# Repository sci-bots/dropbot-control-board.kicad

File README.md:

# DropBot v3 control board

The control board is a component of the [DropBot system][dropbot] responsible for:

* serial communication with the host computer (via USB)
* generation of the high-voltage driving signal (up to 140V @ < 10 kHz)
* impedance-measurement (for estimating drop position, velocity, etc.)
* control of other system hardware (e.g., switching boards)

For more information, please visit https://sci-bots.com

[][sci-bots]

This design is open-source hardware released under a [Creative Commons Attribution-ShareAlike licence][cc-by-sa].

[][cc-by-sa]

[dropbot]: https://github.com/sci-bots/dropbot-v3
[sci-bots]: https://sci-bots.com/
[cc-by-sa]: http://creativecommons.org/licenses/by-sa/3.0

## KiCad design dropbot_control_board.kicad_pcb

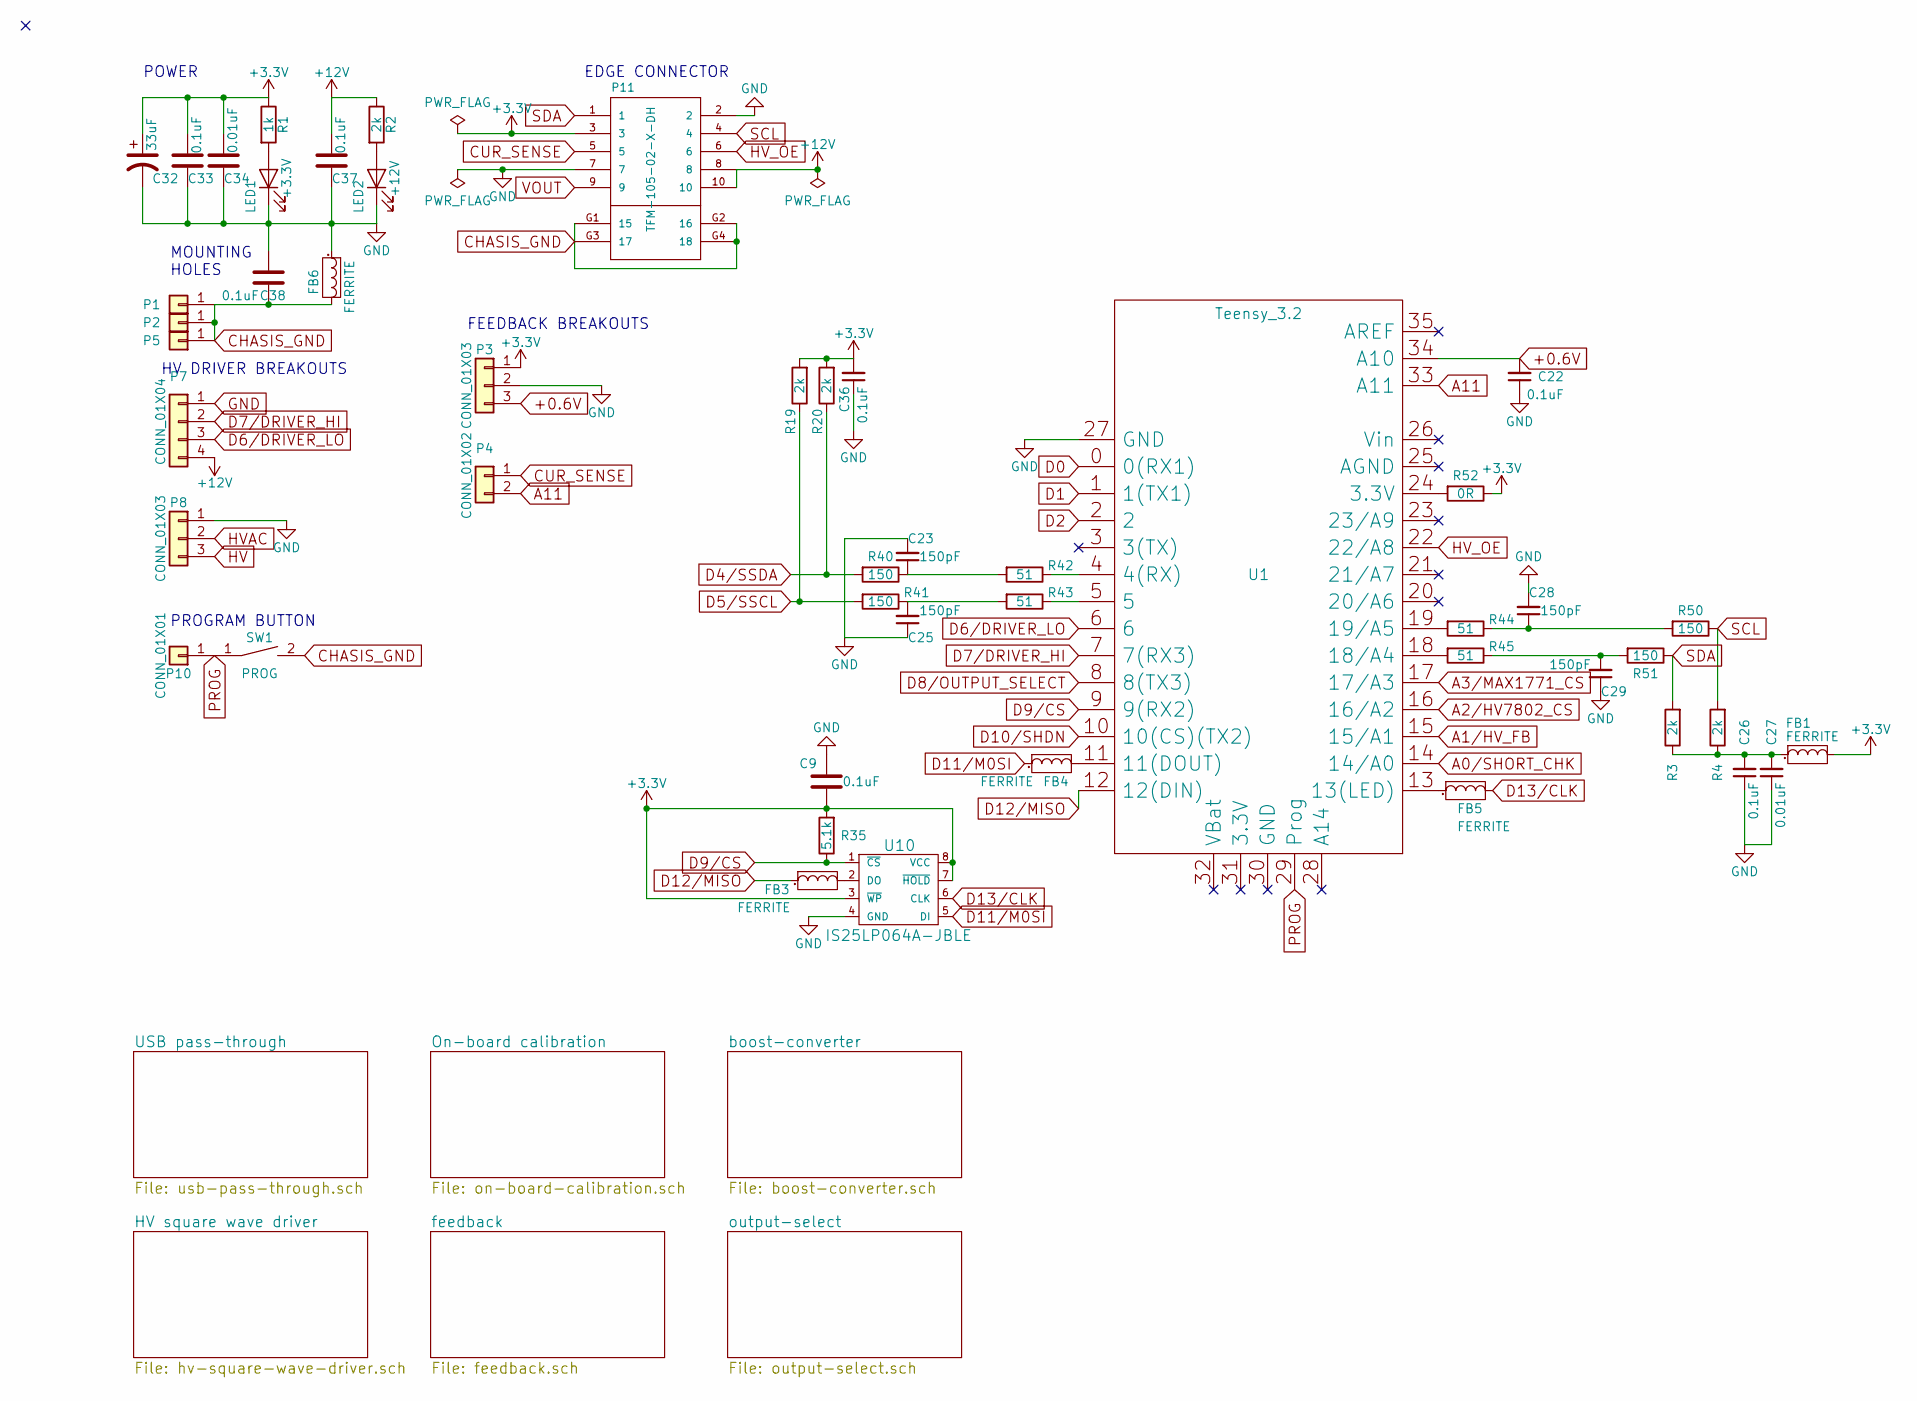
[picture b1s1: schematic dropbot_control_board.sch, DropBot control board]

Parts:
C9, C22, C26, C33, C36, C37, C38: 0.1uF; C_0805; MPN CL21B104KBCNNNC
C23, C25, C28, C29: 150pF; C_0805; MPN CL21C151JBANNNC
C27, C34: 0.01uF; C_0805; MPN CC0805KRX7R9BB103
C32: 33uF; SM2917; MPN T491D336K020AT
FB1, FB3, FB4, FB5, FB6: FERRITE; R_0805; MPN 742792040
LED1: +3.3V; LED_0805; MPN 150080BS75000
LED2: +12V; LED_0805; MPN 150080BS75000
P1, P2, P5: CONN_01X01; 1pin; MPN DNP
P3: CONN_01X03; Pin_Header_Straight_1x03_Pitch2.54mm; MPN DNP
P4: CONN_01X02; Pin_Header_Straight_1x02_Pitch2.54mm; MPN DNP
P7: CONN_01X04; Pin_Header_Straight_1x04; MPN DNP
P8: CONN_01X03; Pin_Header_Straight_1x03; MPN DNP
P10: CONN_01X01; Pin_Header_Straight_1x01_Pitch2.54mm; MPN DNP
P11: TFM-105-02-X-DH; MPN TFM-105-02-L-DH
R1: 1k; R_0805; MPN RC0805FR-071KL
R2, R3, R4, R19, R20: 2k; R_0805; MPN RC0805FR-072KL
R35: 5.1k; R_0805; MPN RC0805FR-075K1L
R40, R41, R50, R51: 150; R_0805; MPN RC0805FR-07150RL
R42, R43, R44, R45: 51; R_0805; MPN RC0805FR-0751RL
R52: 0R; R_0805; MPN RC0805JR-070RL
SW1: PROG; PTS840_GK_SMTR_LFS; MPN PTS840 GK SMTR LFS
U1: Teensy_3.2; Teensy-3.2; MPN DNP
U10: IS25LP064A-JBLE; SSO-8_5.2x5.2mm_Pitch1.27mm; MPN IS25LP064A-JBLE

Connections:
+0.6V: C22.2, P3.3, U1.34 (A10); also elsewhere on the board
+3V3: C9.1, C32.1, C33.2, C34.2, C36.2, FB1.2, P3.1, P11.3, R1.1, R19.2, R20.2, R35.2, R52.1, U10.3 (~WP), U10.7 (~HOLD), U10.8 (VCC); also elsewhere on the board
+12V: C37.2, P7.4, P11.8, P11.10, R2.1; also elsewhere on the board
A0/SHORT_CHK: U1.14 (14/A0); also elsewhere on the board
A1/HV_FB: U1.15 (15/A1); also elsewhere on the board
A2/HV7802_CS: U1.16 (16/A2); also elsewhere on the board
A3/MAX1771_CS: U1.17 (17/A3); also elsewhere on the board
A6: U1.20 (20/A6)
A7: U1.21 (21/A7)
A11: P4.2, U1.33 (A11); also elsewhere on the board
CHASIS_GND: C38.1, FB6.2, P1.1, P2.1, P5.1, P11.G1 (15), P11.G2 (16), P11.G3 (17), P11.G4 (18), SW1.2, SW1.3; also elsewhere on the board
CUR_SENSE: P4.1, P11.5; also elsewhere on the board
D0: U1.0 (0(RX1)); also elsewhere on the board
D1: U1.1 (1(TX1)); also elsewhere on the board
D2: U1.2; also elsewhere on the board
D4/SSDA: R20.1, R40.2; also elsewhere on the board
D5/SSCL: R19.1, R41.2; also elsewhere on the board
D6/DRIVER_LO: P7.3, U1.6; also elsewhere on the board
D7/DRIVER_HI: P7.2, U1.7 (7(RX3)); also elsewhere on the board
D8/OUTPUT_SELECT: U1.8 (8(TX3)); also elsewhere on the board
D9/CS: R35.1, U1.9 (9(RX2)), U10.1 (~CS)
D10/SHDN: U1.10 (10(CS)(TX2)); also elsewhere on the board
D11/M0SI: FB4.1, U10.5 (DI)
D12/MISO: FB3.1, U1.12 (12(DIN))
D13/CLK: FB5.2, U10.6 (CLK)
GND: C9.2, C22.1, C23.2, C25.1, C26.1, C27.1, C28.2, C29.1, C32.2, C33.1, C34.1, C36.1, C37.1, C38.2, FB6.1, LED1.1 (K), LED2.1 (K), P3.2, P7.1, P8.1, P11.2, P11.7, U1.27 (GND), U10.4 (GND); also elsewhere on the board
HV: P8.3; also elsewhere on the board
HVAC: P8.2; also elsewhere on the board
HV_OE: P11.6, U1.22 (22/A8); also elsewhere on the board
unnamed: C23.1, R40.1, R42.2
unnamed: C25.2, R41.1, R43.2
unnamed: C26.2, C27.2, FB1.1, R3.1, R4.1
unnamed: C28.1, R44.1, R50.2
unnamed: C29.2, R45.1, R51.2
unnamed: FB3.2, U10.2 (DO)
unnamed: FB4.2, U1.11 (11(DOUT))
unnamed: FB5.1, U1.13 (13(LED))
unnamed: LED1.2 (A), R1.2
unnamed: LED2.2 (A), R2.2
unnamed: R42.1, U1.4 (4(RX))
unnamed: R43.1, U1.5
unnamed: R44.2, U1.19 (19/A5)
unnamed: R45.2, U1.18 (18/A4)
unnamed: R52.2, U1.24 (3.3V)
PROG: P10.1, SW1.1, U1.29 (Prog)
SCL: P11.4, R4.2, R50.1
SDA: P11.1, R3.2, R51.1
VOUT: P11.9; also elsewhere on the board

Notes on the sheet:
EDGE CONNECTOR
HV DRIVER BREAKOUTS
FEEDBACK BREAKOUTS
MOUNTING HOLES
PROGRAM BUTTON
POWER

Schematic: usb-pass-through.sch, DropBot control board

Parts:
C39: 0.1uF; C_0805; MPN CL21B104KBCNNNC
D5: WE-TVS_824015; wurth-WE-TVS_SOT23-6L; MPN 824015
FB7, FB8: FERRITE; R_0805; MPN 742792040
L2: 90 Ohm@100MHz; wurth-WE-CNSW_0805; MPN 744231091
P6: USB_B; 1734346-1; MPN 1734346-1
P9: USB_A; AU-Y1006; MPN AU-Y1006

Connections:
CHASIS_GND: C39.1, D5.2 (GND), P6.4, P6.5; also elsewhere on the board
D+: L2.2, P9.3
D-: L2.3, P9.2
GND: P9.4, P9.5; also elsewhere on the board
unnamed: C39.2, FB7.2, FB8.1
unnamed: D5.1, D5.3, L2.1, P6.3
unnamed: D5.4, D5.6, L2.4, P6.2
unnamed: D5.5 (VDD), FB7.1, P6.1
unnamed: FB8.2, P9.1

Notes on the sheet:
USB PASSTHROUGH Includes ESD protection and EMI suppression (See Wurth Electronics App Note ANP002C).

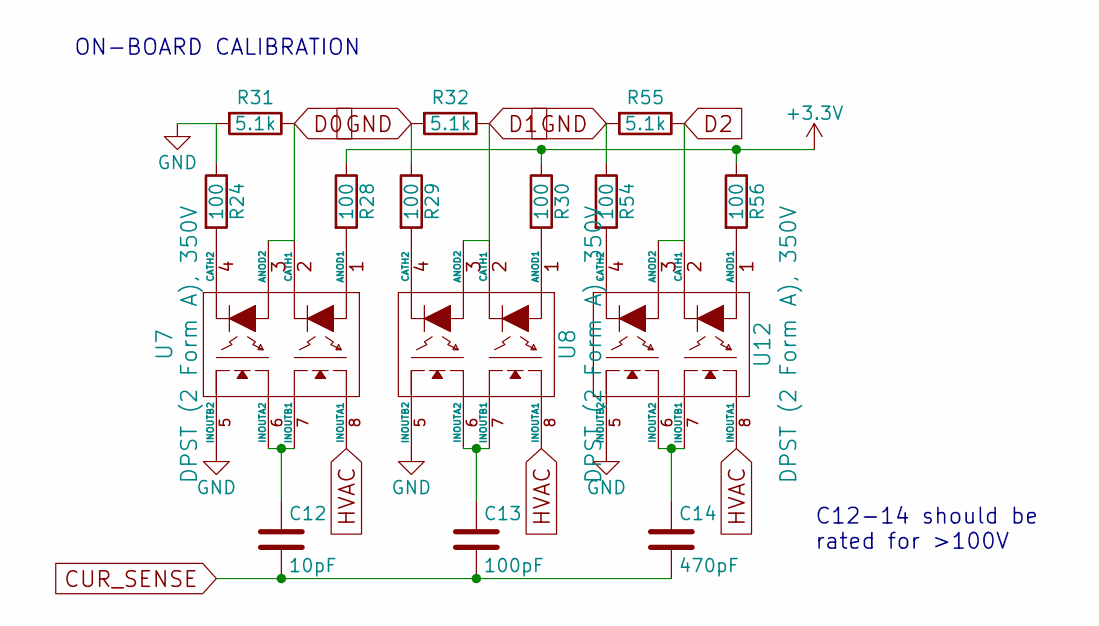
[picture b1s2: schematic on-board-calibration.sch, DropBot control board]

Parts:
C12: 10pF; C_0805; MPN CL21C100JECNNWC
C13: 100pF; C_0805; MPN CL21C101JECNNWC
C14: 470pF; C_0805; MPN CL21C471JDFNNWG
R24, R28, R29, R30, R54, R56: 100; R_0805; MPN RC0805FR-07100RL
R31, R32, R55: 5.1k; R_0805; MPN RC0805FR-075K1L
U7, U8, U12: DPST (2 Form A), 350V; DIP-8_SMD; MPN TLP227G-2(TP1,N,F)

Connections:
+3V3: R28.1, R30.1, R56.1; also elsewhere on the board
CUR_SENSE: C12.2, C13.2, C14.2; also elsewhere on the board
D0: R31.1, U7.2 (CATH1), U7.3 (ANOD2); also elsewhere on the board
D1: R32.1, U8.2 (CATH1), U8.3 (ANOD2); also elsewhere on the board
D2: R55.1, U12.2 (CATH1), U12.3 (ANOD2); also elsewhere on the board
GND: R24.1, R29.1, R31.2, R32.2, R54.1, R55.2, U7.5 (INOUTB2), U8.5 (INOUTB2), U12.5 (INOUTB2); also elsewhere on the board
HVAC: U7.8 (INOUTA1), U8.8 (INOUTA1), U12.8 (INOUTA1); also elsewhere on the board
unnamed: C12.1, U7.6 (INOUTA2), U7.7 (INOUTB1)
unnamed: C13.1, U8.6 (INOUTA2), U8.7 (INOUTB1)
unnamed: C14.1, U12.6 (INOUTA2), U12.7 (INOUTB1)
unnamed: R24.2, U7.4 (CATH2)
unnamed: R28.2, U7.1 (ANOD1)
unnamed: R29.2, U8.4 (CATH2)
unnamed: R30.2, U8.1 (ANOD1)
unnamed: R54.2, U12.4 (CATH2)
unnamed: R56.2, U12.1 (ANOD1)

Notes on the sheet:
ON-BOARD CALIBRATION
C12-14 should be rated for >100V

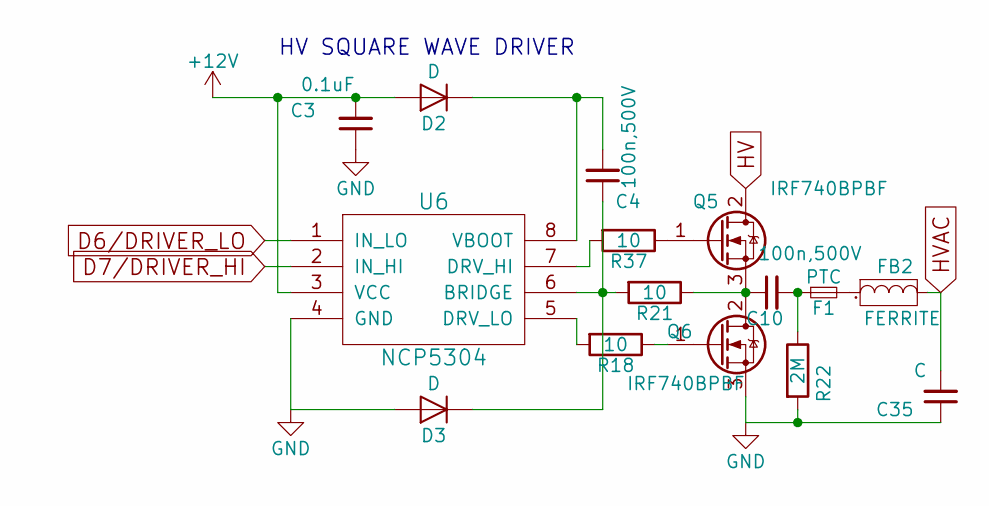
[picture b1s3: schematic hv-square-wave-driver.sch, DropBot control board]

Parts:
C3: 0.1uF; C_0805; MPN CL21B104KBCNNNC
C4, C10: 100n,500V; C_1210; MPN C1210C104KCRACTU
C35: C; C_1206; MPN DNP
D2, D3: D; SMA_Standard; MPN US1J-13-F
F1: PTC; Resistor_Vertical_RM5mm; MPN B59773B0120A070
FB2: FERRITE; R_0805; MPN 742792040
Q5, Q6: IRF740BPBF; TO-220_Neutral123_Horizontal_LargePads; MPN IRF740BPBF
R18, R21, R37: 10; R_0805; MPN RC0805FR-0710RL
R22: 2M; R_1206; MPN HVCB1206KDL2M00
U6: NCP5304; SOIC-8-N; MPN NCP5304DR2G

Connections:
+12V: C3.2, D2.2 (A), U6.3 (VCC); also elsewhere on the board
D6/DRIVER_LO: U6.1 (IN_LO); also elsewhere on the board
D7/DRIVER_HI: U6.2 (IN_HI); also elsewhere on the board
GND: C3.1, C35.1, D3.2 (A), Q6.3 (S), R22.2, U6.4 (GND); also elsewhere on the board
HV: Q5.2 (D); also elsewhere on the board
HVAC: C35.2, FB2.2; also elsewhere on the board
unnamed: C4.1, D3.1 (K), R21.2, U6.6 (BRIDGE)
unnamed: C4.2, D2.1 (K), U6.8 (VBOOT)
unnamed: C10.1, Q5.3 (S), Q6.2 (D), R21.1
unnamed: C10.2, F1.1, R22.1
unnamed: F1.2, FB2.1
unnamed: Q5.1 (G), R37.1
unnamed: Q6.1 (G), R18.1
unnamed: R18.2, U6.5 (DRV_LO)
unnamed: R37.2, U6.7 (DRV_HI)

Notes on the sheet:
HV SQUARE WAVE DRIVER

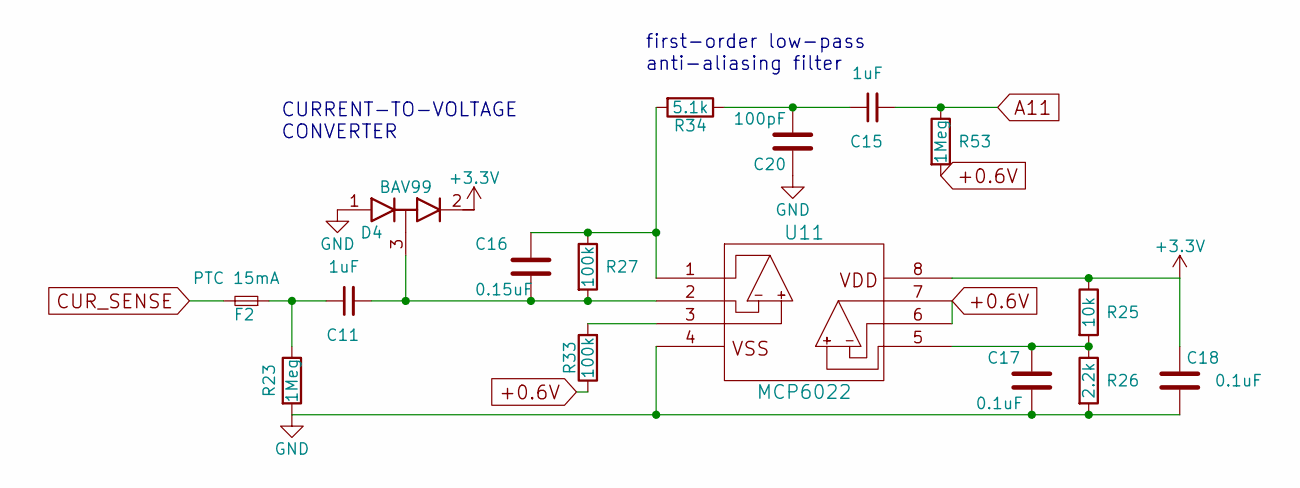
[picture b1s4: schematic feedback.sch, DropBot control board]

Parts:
C11, C15: 1uF; C_0805; MPN CC0805KKX7R9BB105
C16: 0.15uF; C_0805; MPN 08053C154JAT2A
C17, C18: 0.1uF; C_0805; MPN CL21B104KBCNNNC
C20: 100pF; C_0805; MPN CL21C101JECNNWC
D4: BAV99; SOT-23; MPN TBAV99,LM
F2: PTC 15mA; R_1210; MPN B59807A0090A062
R23, R53: 1Meg; R_0805; MPN RC0805FR-071ML
R25: 10k; R_0805; MPN RC0805FR-0710KL
R26: 2.2k; R_0805; MPN RC0805FR-072K2L
R27, R33: 100k; R_0805; MPN RC0805FR-07100KL
R34: 5.1k; R_0805; MPN RC0805FR-075K1L
U11: MCP6022; DIP-8_W7.62mm; MPN ED08DT

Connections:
+0.6V: R33.1, R53.2, U11.6 (VINB-), U11.7 (VOUTB); also elsewhere on the board
+3V3: C18.1, D4.2 (K), R25.1, U11.8 (VDD); also elsewhere on the board
A11: C15.2, R53.1; also elsewhere on the board
CUR_SENSE: F2.2; also elsewhere on the board
GND: C17.2, C18.2, C20.1, D4.1 (A), R23.2, R26.2, U11.4 (VSS); also elsewhere on the board
unnamed: C11.1, F2.1, R23.1
unnamed: C11.2, C16.2, D4.3 (common), R27.2, U11.2 (VINA-)
unnamed: C15.1, C20.2, R34.1
unnamed: C16.1, R27.1, R34.2, U11.1 (VOUTA)
unnamed: C17.1, R25.2, R26.1, U11.5 (VINB+)
unnamed: R33.2, U11.3 (VINA+)

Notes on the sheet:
first-order low-pass anti-aliasing filter
CURRENT-TO-VOLTAGE CONVERTER

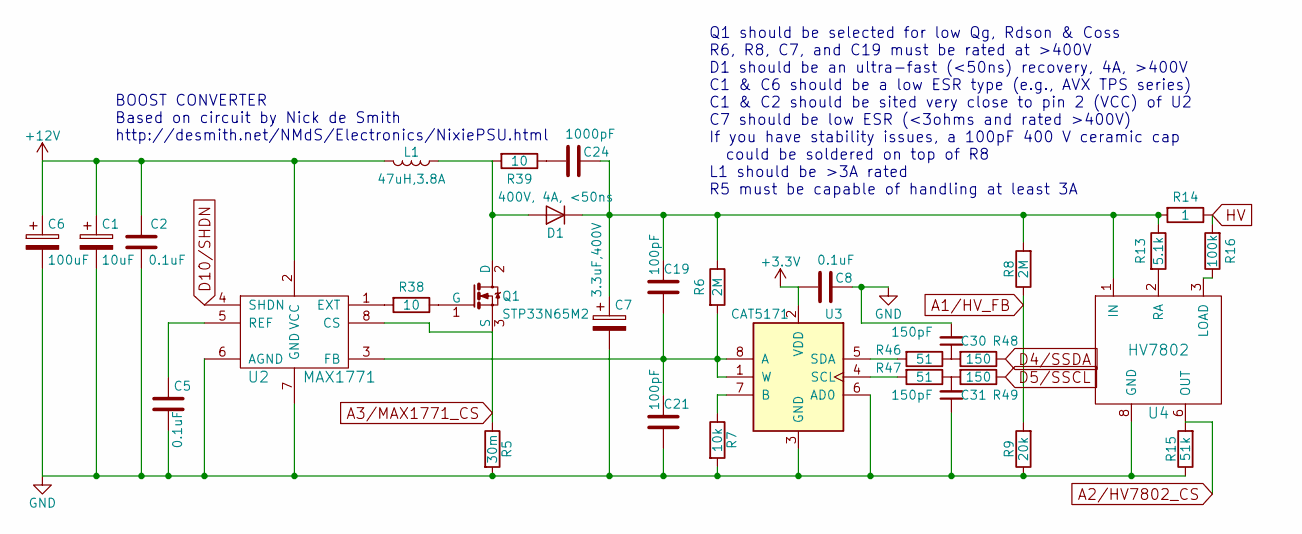
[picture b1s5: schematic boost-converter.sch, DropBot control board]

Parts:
C1: 10uF; TantalC_SizeD_EIA-7343_Reflow; MPN T494D106M025AT
C2, C5, C8: 0.1uF; C_0805; MPN CL21B104KBCNNNC
C6: 100uF; TantalC_SizeE_EIA-7360_Reflow; MPN T491X107K025AT
C7: 3.3uF,400V; c_elec_10x10; MPN EEV-EB2G3R3Q
C19, C21: 100pF; C_0805; MPN CL21C101JECNNWC
C24: 1000pF; C_0805; MPN 501R15W102KV4E
C30, C31: 150pF; C_0805; MPN CL21C151JBANNNC
D1: 400V, 4A, <50ns; SMC_Standard; MPN VS-4EGU06-M3/5BT
L1: 47uH,3.8A; SRR1210; MPN SRR1210-470M
Q1: STP33N65M2; TO-220_Neutral123_Horizontal_LargePads; MPN STP33N65M2
R5: 30m; R_2512; MPN CSR2512C0R03F
R6, R8: 2M; R_1206; MPN HVCB1206KDL2M00
R7: 10k; R_0805; MPN RC0805FR-0710KL
R9: 20k; R_0805; MPN RC0805FR-0720KL
R13: 5.1k; R_0805; MPN RC0805FR-075K1L
R14: 1; R_0805; MPN ERJ-6DQJ1R0V
R15: 51k; R_0805; MPN RC0805FR-0751KL
R16: 100k; R_0805; MPN RC0805FR-07100KL
R38, R39: 10; R_0805; MPN RC0805FR-0710RL
R46, R47: 51; R_0805; MPN RC0805FR-0751RL
R48, R49: 150; R_0805; MPN RC0805FR-07150RL
U2: MAX1771; SOIC-8_3.9x4.9mm_Pitch1.27mm; MPN MAX1771ESA+
U3: CAT5171; SOT-23-8; MPN CAT5171TBI-50GT3
U4: HV7802; MSOP-8; MPN HV7802MG-G

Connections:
+3V3: C8.2, U3.2 (VDD); also elsewhere on the board
+12V: C1.1, C2.2, C6.1, L1.2, U2.2 (VCC); also elsewhere on the board
A1/HV_FB: R8.1, R9.2; also elsewhere on the board
A2/HV7802_CS: R15.2, U4.6 (OUT); also elsewhere on the board
A3/MAX1771_CS: Q1.3 (S), R5.1, U2.8 (CS); also elsewhere on the board
D4/SSDA: R48.1; also elsewhere on the board
D5/SSCL: R49.1; also elsewhere on the board
D10/SHDN: U2.4 (SHDN); also elsewhere on the board
GND: C1.2, C2.1, C5.2, C6.2, C7.2, C8.1, C21.1, C30.2, C31.1, R5.2, R7.2, R9.1, R15.1, U2.6 (AGND), U2.7 (GND), U3.3 (GND), U3.6 (AD0), U4.8 (GND); also elsewhere on the board
HV: R14.1, R16.2; also elsewhere on the board
unnamed: C5.1, U2.5 (REF)
unnamed: C19.1, C21.2, R6.2, U2.3 (FB), U3.1 (W), U3.8 (A)
unnamed: C7.1, C19.2, C24.1, D1.1 (K), R6.1, R8.2, R13.1, R14.2, U4.1 (IN)
unnamed: C24.2, R39.1
unnamed: C30.1, R46.1, R48.2
unnamed: C31.2, R47.1, R49.2
unnamed: D1.2 (A), L1.1, Q1.2 (D), R39.2
unnamed: Q1.1 (G), R38.1
unnamed: R7.1, U3.7 (B)
unnamed: R13.2, U4.2 (RA)
unnamed: R16.1, U4.3 (LOAD)
unnamed: R38.2, U2.1 (EXT)
unnamed: R46.2, U3.5 (SDA)
unnamed: R47.2, U3.4 (SCL)

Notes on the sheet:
BOOST CONVERTER Based on circuit by Nick de Smith http://desmith.net/NMdS/Electronics/NixiePSU.html
Q1 should be selected for low Qg, Rdson & Coss R6, R8, C7, and C19 must be rated at >400V D1 should be an ultra-fast (<50ns) recovery, 4A, >400V C1 & C6 should be a low ESR type (e.g., AVX TPS series) C1 & C2 should be sited very close to pin 2 (VCC) of U2 C7 should be low ESR (<3ohms and rated >40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

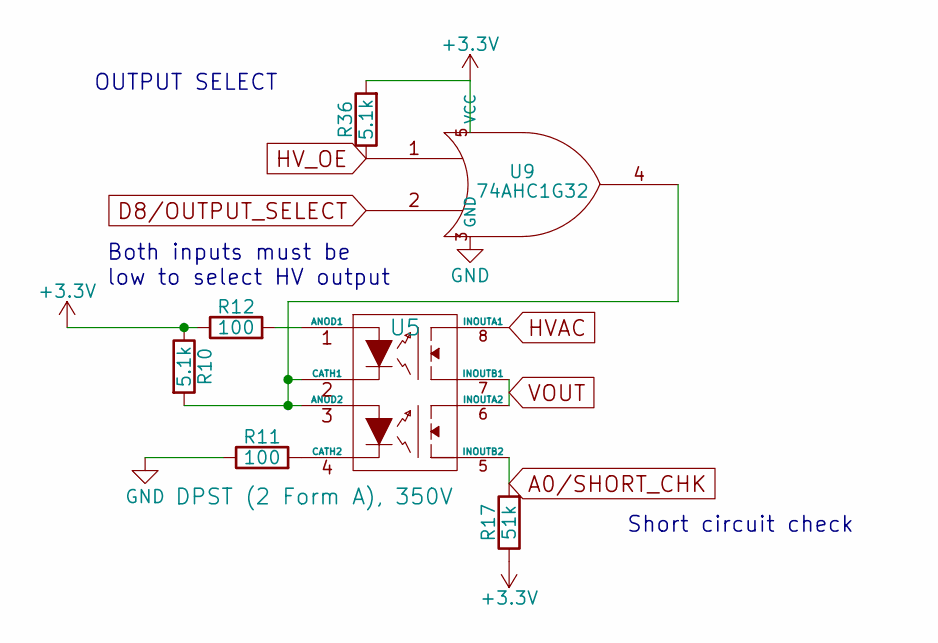
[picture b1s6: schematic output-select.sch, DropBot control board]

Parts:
R10, R36: 5.1k; R_0805; MPN RC0805FR-075K1L
R11, R12: 100; R_0805; MPN RC0805FR-07100RL
R17: 51k; R_0805; MPN RC0805FR-0751KL
U5: DPST (2 Form A), 350V; DIP-8_SMD; MPN TLP227G-2(TP1,N,F)
U9: 74AHC1G32; SOT-353; MPN 74AHC1G32GW,125

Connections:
+3V3: R10.1, R12.1, R17.1, R36.2, U9.5 (VCC); also elsewhere on the board
A0/SHORT_CHK: R17.2, U5.5 (INOUTB2); also elsewhere on the board
D8/OUTPUT_SELECT: U9.2; also elsewhere on the board
GND: R11.1, U9.3 (GND); also elsewhere on the board
HVAC: U5.8 (INOUTA1); also elsewhere on the board
HV_OE: R36.1, U9.1; also elsewhere on the board
unnamed: R10.2, U5.2 (CATH1), U5.3 (ANOD2), U9.4
unnamed: R11.2, U5.4 (CATH2)
unnamed: R12.2, U5.1 (ANOD1)
VOUT: U5.6 (INOUTA2), U5.7 (INOUTB1); also elsewhere on the board

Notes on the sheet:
OUTPUT SELECT
Both inputs must be low to select HV output
Short circuit check

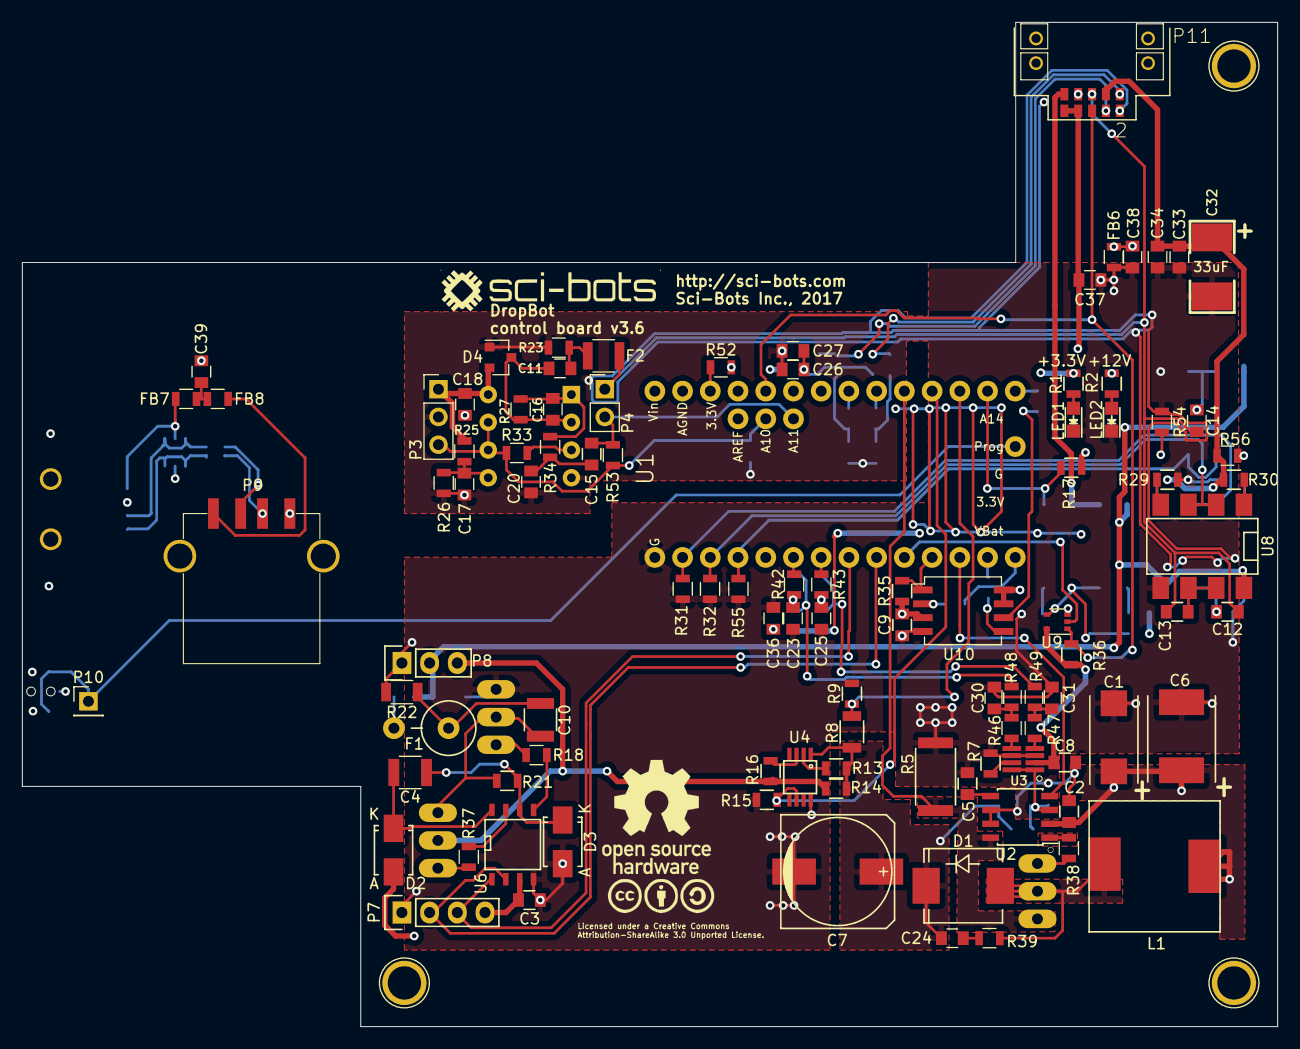
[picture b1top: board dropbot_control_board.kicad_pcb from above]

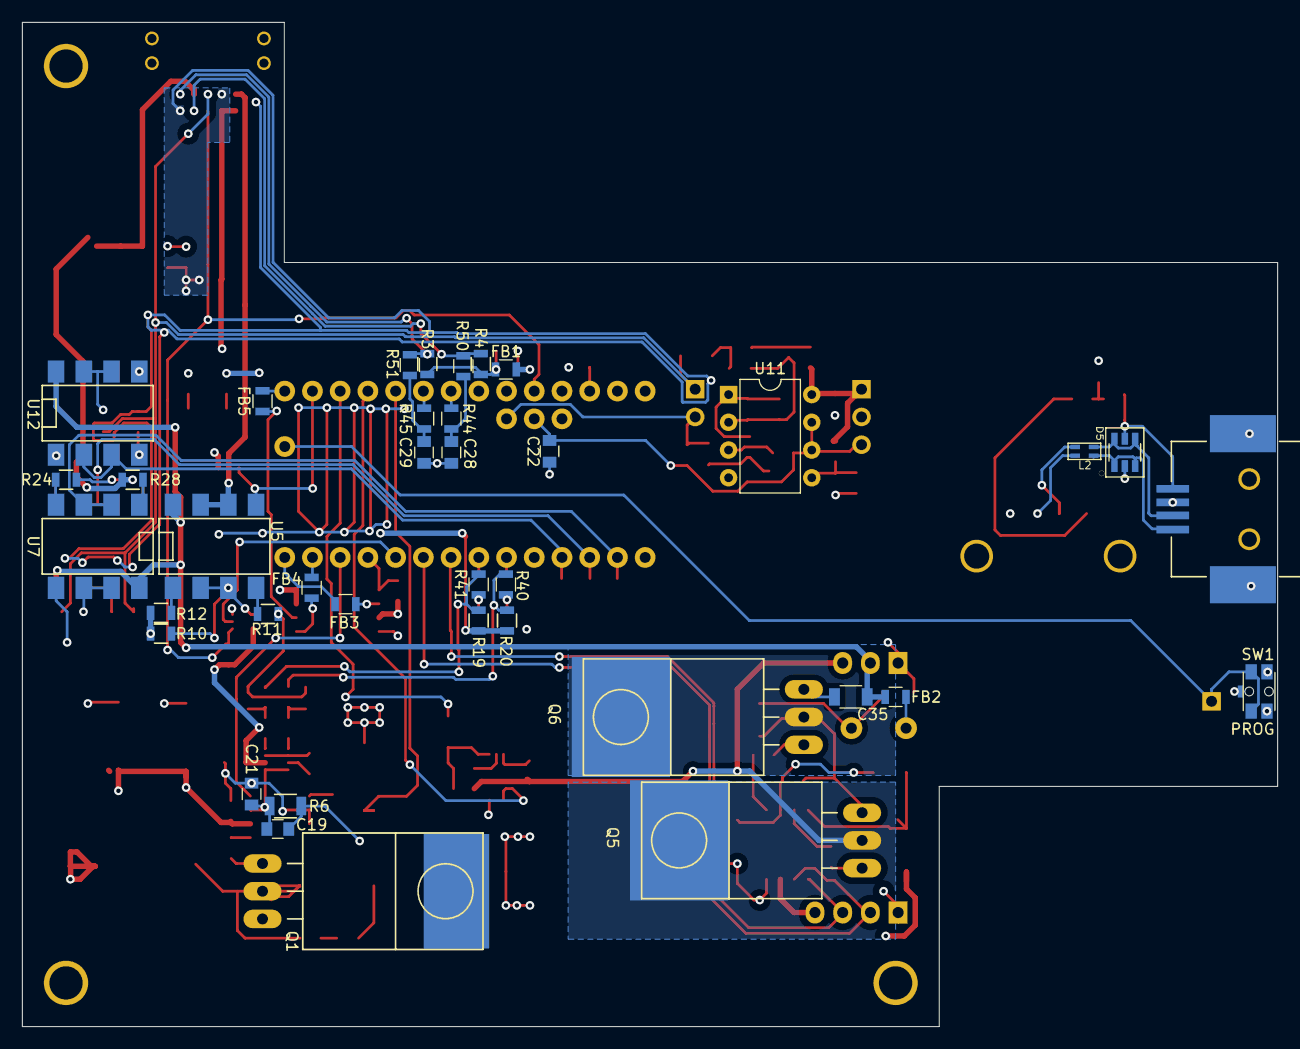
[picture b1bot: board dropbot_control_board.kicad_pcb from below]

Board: 4 copper layers, 115.0 x 92.0 mm, 141 parts (38 on the bottom side), 94 nets.

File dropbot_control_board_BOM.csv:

Reference,Value,Footprint,Count,Datasheet,Mfg_Part_No
"LED2, LED1","+12V, +3.3V",LEDs:LED_0805,2,,150080BS75000
"R2, R3, R4, R19, R20",2k,Resistors_SMD:R_0805,5,,RC0805FR-072KL
R1,1k,Resistors_SMD:R_0805,1,,RC0805FR-071KL
P8,CONN_01X03,Pin_Headers:Pin_Header_Straight_1x03,1,,
P7,CONN_01X04,Pin_Headers:Pin_Header_Straight_1x04,1,,
"R35, R31, R32, R55, R34, R13, R10, R36",5.1k,Resistors_SMD:R_0805,8,,RC0805FR-075K1L
U10,IS25LP064A-JBLE,Sci-Bots:SSO-8_5.2x5.2mm_Pitch1.27mm,1,https://www.winbond.com/resource-files/w25q64fv%20revq%20061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,IS25LP064A-JBLE
"C9, C26, C33, C36, C37, C38, C22, C39, C3, C17, C18, C5, C8, C2",0.1uF,Capacitors_SMD:C_0805,14,,CL21B104KBCNNNC
P11,TFM-105-02-X-DH,Sci-Bots:TFM-105-02-X-DH,1,,TFM-105-02-L-DH
"R45, R44, R43, R42, R46, R47",51,Resistors_SMD:R_0805,6,,RC0805FR-0751RL
"C28, C29, C25, C23, C30, C31",150pF,Capacitors_SMD:C_0805,6,,CL21C151JBANNNC
"R51, R50, R41, R40, R48, R49",150,Resistors_SMD:R_0805,6,,RC0805FR-07150RL
"FB1, FB4, FB3, FB5, FB6, FB7, FB8, FB2","FERRITE, 600 Ohm@100MHz, 600 Ohm@100MHz, FERRITE",Resistors_SMD:R_0805,8,,742792040
"C27, C34",0.01uF,Capacitors_SMD:C_0805,2,,CC0805KRX7R9BB103
C32,33uF,Sci-Bots:SM2917,1,,T491D336K020AT
"P1, P2, P5",CONN_01X01,Connect:1pin,3,,
U1,Teensy_3.2,Sci-Bots:Teensy-3.2,1,,
R52,0R,Resistors_SMD:R_0805,1,,RC0805JR-070RL
SW1,PROG,Sci-Bots:PTS840_GK_SMTR_LFS,1,,PTS840 GK SMTR LFS
P10,CONN_01X01,Pin_Headers:Pin_Header_Straight_1x01_Pitch2.54mm,1,,
P3,CONN_01X03,Pin_Headers:Pin_Header_Straight_1x03_Pitch2.54mm,1,,
P4,CONN_01X02,Pin_Headers:Pin_Header_Straight_1x02_Pitch2.54mm,1,,
D5,WE-TVS_824015,Sci-Bots:wurth-WE-TVS_SOT23-6L,1,,824015
L2,90 Ohm@100MHz,Sci-Bots:wurth-WE-CNSW_0805,1,,744231091
P6,USB_B,Sci-Bots:1734346-1,1,,1734346-1
P9,USB_A,Sci-Bots:AU-Y1006,1,,AU-Y1006
"U7, U8, U12, U5","DPST (2 Form A), 350V",SMD_Packages:DIP-8_SMD,4,,"TLP227G-2(TP1,N,F)"
C12,10pF,Capacitors_SMD:C_0805,1,,CL21C100JECNNWC
"R24, R28, R29, R30, R54, R56, R12, R11",100,Resistors_SMD:R_0805,8,,RC0805FR-07100RL
"C13, C20, C19, C21",100pF,Capacitors_SMD:C_0805,4,,CL21C101JECNNWC
C14,470pF,Capacitors_SMD:C_0805,1,,CL21C471JDFNNWG
U6,NCP5304,SMD_Packages:SOIC-8-N,1,,NCP5304DR2G
"D2, D3",D,Diodes_SMD:SMA_Standard,2,,US1J-13-F
"R21, R37, R18, R38, R39",10,Resistors_SMD:R_0805,5,,RC0805FR-0710RL
"R22, R6, R8",2M,Resistors_SMD:R_1206,3,,HVCB1206KDL2M00
"Q5, Q6",IRF740BPBF,TO_SOT_Packages_THT:TO-220_Neutral123_Horizontal_LargePads,2,,IRF740BPBF
"C4, C10","100n,500V",Capacitors_SMD:C_1210,2,,C1210C104KCRACTU
C35,C,Capacitors_SMD:C_1206,1,,
F1,PTC,Resistors_ThroughHole:Resistor_Vertical_RM5mm,1,,B59773B0120A070
"R25, R7",10k,Resistors_SMD:R_0805,2,,RC0805FR-0710KL
R26,2.2k,Resistors_SMD:R_0805,1,,RC0805FR-072K2L
"R27, R33, R16",100k,Resistors_SMD:R_0805,3,,RC0805FR-07100KL
C16,0.15uF,Capacitors_SMD:C_0805,1,,08053C154JAT2A
"R23, R53",1Meg,Resistors_SMD:R_0805,2,,RC0805FR-071ML
F2,PTC 15mA,Resistors_SMD:R_1210,1,,B59807A0090A062
D4,BAV99,TO_SOT_Packages_SMD:SOT-23,1,,"TBAV99,LM"
"C11, C15",1uF,Capacitors_SMD:C_0805,2,,CC0805KKX7R9BB105
U11,MCP6022,Housings_DIP:DIP-8_W7.62mm,1,,ED08DT
C6,100uF,Capacitors_Tantalum_SMD:TantalC_SizeE_EIA-7360_Reflow,1,,T491X107K025AT
L1,"47uH,3.8A",footprints:SRR1210,1,,SRR1210-470M
D1,"400V, 4A, <50ns",Diodes_SMD:SMC_Standard,1,,VS-4EGU06-M3/5BT
C7,"3.3uF,400V",Capacitors_SMD:c_elec_10x10,1,,EEV-EB2G3R3Q
U2,MAX1771,Housings_SOIC:SOIC-8_3.9x4.9mm_Pitch1.27mm,1,,MAX1771ESA+ 
Q1,STP33N65M2,TO_SOT_Packages_THT:TO-220_Neutral123_Horizontal_LargePads,1,,STP33N65M2
R5,30m,Resistors_SMD:R_2512,1,,CSR2512C0R03F
R9,20k,Resistors_SMD:R_0805,1,,RC0805FR-0720KL
U4,HV7802,footprints:MSOP-8,1,,HV7802MG-G
R14,1,Resistors_SMD:R_0805,1,,ERJ-6DQJ1R0V
"R15, R17",51k,Resistors_SMD:R_0805,2,,RC0805FR-0751KL
C1,10uF,Capacitors_Tantalum_SMD:TantalC_SizeD_EIA-7343_Reflow,1,,T494D106M025AT
U3,CAT5171,Sci-Bots:SOT-23-8,1,http://www.onsemi.com/pub_link/Collateral/CAT5171-D.PDF,CAT5171TBI-50GT3
C24,1000pF,Capacitors_SMD:C_0805,1,,501R15W102KV4E
U9,74AHC1G32,TO_SOT_Packages_SMD:SOT-353,1,http://www.nxp.com/documents/data_sheet/74AHC_AHCT1G32.pdf,"74AHC1G32GW,125"

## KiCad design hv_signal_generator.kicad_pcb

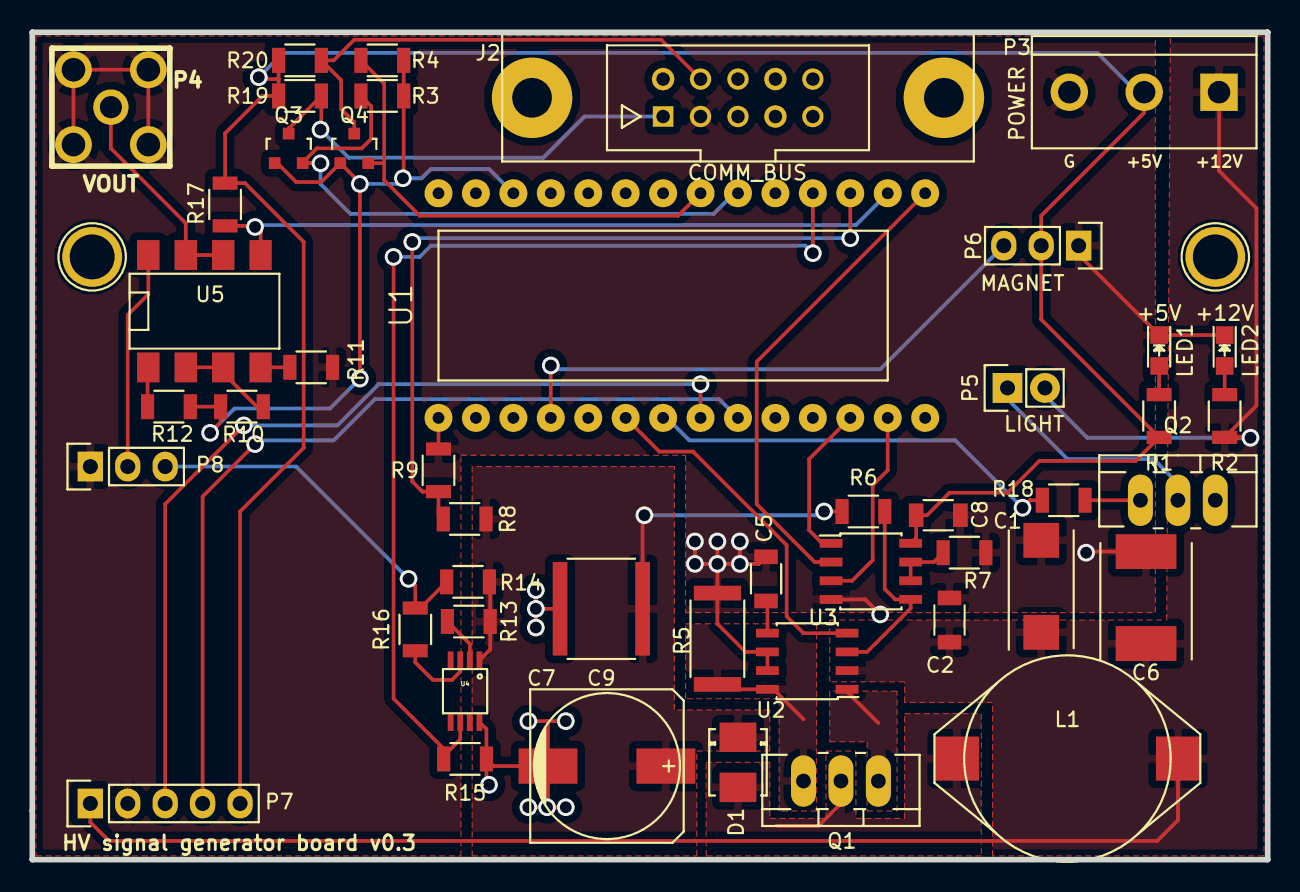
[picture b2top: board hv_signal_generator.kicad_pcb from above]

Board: 2 copper layers, 83.8 x 56.1 mm, 47 parts (0 on the bottom side), 38 nets.

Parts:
C1: 10uF; TantalC_SizeD_EIA-7343_Reflow
C2, C5, C8: 0.1uF; C_1206
C6: 100uF,35V; TantalC_SizeE_EIA-7360_Reflow
C7: 3.3uF,400V; c_elec_10x10
C9: 100nF,400V; C_2225
D1: ES2F; DO-214BA
J2: COMM_BUS; he10-10d
L1: 100uH; DU1971
LED1: +5V; LED_0805
LED2: +12V; LED_0805
P3: POWER; bornier3
P4: VOUT; JACK_SMA
P5: LIGHT; Pin_Header_Straight_1x02
P6: MAGNET; Pin_Header_Straight_1x03
P7: CONN_01X05; Pin_Header_Straight_1x05
P8: CONN_01X03; Pin_Header_Straight_1x03
Q1: IRF644PBF; TO-220_Neutral123_Vertical_LargePads
Q2: TIP120; TO-220_Neutral123_Vertical_LargePads
Q3, Q4: 2N7002; SOT-23
R1, R18: 1k; R_1206
R2: 2k; R_1206
R3, R4, R13, R19, R20: 5.1k; R_1206
R5: 50m; R_2512
R6, R8: 1M; R_1206
R7: 4k; R_1206
R9: 20k; R_1206
R10: 4.75k; R_1206
R11, R12: 200; R_1206
R14: 5.1; R_1206
R15, R17: 51k; R_1206
R16: 100k; R_1206
U1: Teensy_3.1; Teensy-3.1
U2: MAX1771; SOIC-8_3.9x4.9mm_Pitch1.27mm
U3: MCP41050; SOIC-8_3.9x4.9mm_Pitch1.27mm
U4: HV7802; MSOP-8
U5: AQW216; DIP-8_SMD

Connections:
+3.3V: Q3.1, Q4.1, R3.1, R4.1, R10.1, R12.2, U1.24
+5V: C8.2, P3.2, P6.2, P7.5, R1.1, R17.1, R19.1, R20.1, U3.8
+12V: C1.1, C2.1, C6.1, L1.2, P3.1, P5.2, P7.1, R2.1, U2.2
A0/SHORT_CHK: R17.2, U1.14, U5.5
A1/HV_FB: R8.1, R9.2, U1.15
A2/CURRENT_SENSE: R15.2, U1.16, U4.6
A3/OUTPUT_SELECT: R10.2, U5.2, U5.3
D2/SERVO: P6.3, U1.2
D4/SHDN: U1.4, U2.4
D5/LED: R18.2, U1.5
D6/DRIVER_HI: P7.3, U1.6
D7/DRIVER_LO: P7.4, U1.7
D10/MCP41050_CS: U1.10, U3.1
D11/MOSI: U1.11, U3.3
D13/SCK: U1.13, U3.2
GND: C1.2, C2.2, C5.2, C6.2, C7.2, C8.1, C9.2, J2.3, LED1.1, LED2.1, P3.3, P4.2, P6.1, P7.2, P8.1, Q2.3, R5.2, R7.2, R9.1, R11.1, R15.1, U1.27, U2.6, U2.7, U3.4, U4.8
HV: P8.3, R14.1, R16.2
unnamed: C5.1, U2.5
unnamed: C7.1, C9.1, D1.1, R6.1, R8.2, R13.1, R14.2, U4.1
unnamed: D1.2, L1.1, Q1.2
unnamed: LED1.2, R1.2
unnamed: LED2.2, R2.2
unnamed: P4.1, U5.6, U5.7
unnamed: P5.1, Q2.2
unnamed: Q1.1, U2.1
unnamed: Q1.3, R5.1, U2.8
unnamed: Q2.1, R18.1
unnamed: R6.2, U2.3, U3.5
unnamed: R7.1, U3.6, U3.7
unnamed: R11.2, U5.4
unnamed: R12.1, U5.1
unnamed: R13.2, U4.2
unnamed: R16.1, U4.3
SCL_3.3V: Q4.2, R4.2, U1.19
SCL_5V: J2.4, Q4.3, R20.2
SDA_3.3V: Q3.2, R3.2, U1.18
SDA_5V: J2.1, Q3.3, R19.2
VOUT: P8.2, U5.8

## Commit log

2016-02-17 Complete layout
2016-02-17 Move C1 and C2 closer to MAX1771 chip and ...
    Add layout notes
2016-02-17 Add clearance between VOUT pin and screw
2016-02-18 Add part numbers to schematic`
2016-04-13 [WIP] Remove HV513, fix orientation of FTDI header
    * fix footprint of L1
2016-04-15 [WIP] Add hv signal generator breakout headers
2016-04-15 Swap parts to support up to 400V and use BJT for LED
2016-04-16 Swap ATMEGA328 for Teensy
2016-04-16 Suppress leading zeros in drill file
2016-04-25 Replace footprint for transistors with SOT-23
2016-09-20 Rename dropbot-control-board
2016-09-21 Fix routing of D3/OUTPUT_SELECT and add MAX1771...
    Fix routing of D3/OUTPUT_SELECT and add MAX1771 current sensing.
2016-09-21 Connect 5V pin on COMM_BUS
2016-09-21 [WIP] Integrate HV square-wave driver (not routed)
2016-09-21 [WIP] Add feedback circuit and on-board calibration
2016-09-22 Re-do layout
2016-09-25 Bump library version
2016-11-23 Minor fixes
    * fix inductor footprint
    * footprints for various HV resistors
    * labels for some resistors/caps
    * remove shorted +12V trace
2016-12-19 Use edge connectors and ...
    * Add SPI flash memory
    * Add HV output enable
    * Make feedback circuit breakout and use DIP op-amp
    * Pass Teensy's USB signals through edge connector
2016-12-19 Update pdfs
2016-12-19 Remove rescue library
2017-01-05 Update BOM
2017-01-05 Fix BOM
2017-01-05 Fix op-amp package in BOM
2017-03-07 EMC related improvements
    * convert to 4-layer board
    * add jumper to connect 3.3V of Teensy
    * put filters on i2c
    * add guard traces around i2c and current-sense lines
    * add ferrites to SPI lines
    * add snubber on SPMS diode
2017-03-16 Lower the resistance of i2c pullups (4.75k --> 2k)
2017-03-21 Add usb passthrough, reset button, ...
    * add usb passthrough
    * add reset button
    * fix bad trace on U5
    * fix part number for C7 (3.3uF instead of 10uF)
2017-04-04 Swap F2 for higher voltage rating, monitor HV_OE
    * swap F2 for 1210 footprint: B59807A90A62 (higher voltage rating)
    * monitor HV_OE with A8
2017-04-05 Change part numbers for i2c filters
2017-04-18 Update BOM with alternate parts for C6 and D4
    These parts were out of stock at Digi-key as of 2017-04-18.
2017-04-20 Update current limit on F2
2017-04-21 Change component for D1
2017-04-25 [WIP] Fix USB-B footprint (P6)
    Fixes #3
2017-04-25 [WIP] Fixes #1: C18 is disconnected
2017-04-25 [WIP] Fixes #2: Change prefixes for J1 and IC1
2017-04-25 [WIP] Silkscreen fixes (Fixes #4)
2017-04-25 Move USB-B and program switch up 1mm
2017-05-17 Fix feedback and on-board calibration and move USB
2017-06-02 Add missing schematic diagrams and change some part numbers
2017-06-05 Change part number for ferrites, add *.pos files
2017-06-19 Improve layout/stability of boost converter, etc.
    * improve layout/stability of boost converter
    * enable on board calibration without HVOE
    * add decoupling cap to 0.6V reference
    * fix footprint for U10
    * add programming wire
2017-08-09 Change value of R7 to 10k
    Fixes #6
2017-08-09 Change EEPROM and swap 150 Ohm resisotors for 100...
    Change EEPROM and swap 150 Ohm resisotors for 100 resistors
    driving the PhotoMOS switches.
2018-07-12 Add README.md, LICENSE.md and graphics
2018-07-12 Update BOM
    2 part numbers (F1 and F2) had typos and updated D4 to a part that
    is more commonly available.
2018-07-12 Fix label of A2, update netlist
2018-07-12 Update schematic to use power ports
2018-07-12 Update to use Sci-Bots library
2021-11-08 Update with kicad-helpers files
2021-11-08 Reorganize files
2021-11-10 Add manufacturing files
2021-11-12 Add tests
2021-11-17 Update submodule
2021-11-17 Fix broken symbols and DRC tests
2021-11-18 Use recursive checkout in github action
2021-11-24 Update kicad_helpers, remove docs, add rescue/cache
2021-11-24 Update github action
2021-11-24 Fixed crlf issue
2021-11-25 Remove "Mfg_Part_No" field (replaced by "MPN")
2021-11-25 Fix #2: Replace R7 with 9.1k resistor
    This should ensure that the max voltage is >140V.
2021-11-25 Add badges to README
2021-11-25 Update kitspace badge
2021-11-25 Update netlist
2021-11-25 Add DRC filters

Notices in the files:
dropbot_control_board.kicad_pcb:
Licensed under a Creative Commons
Attribution-ShareAlike 3.0 Unported License.
